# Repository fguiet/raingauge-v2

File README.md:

# Raingauge v2

## The final project

This project is available on Thingiverse : <https://www.thingiverse.com/thing:6480016>

## PCB representation

## 3D representation

## Compute how much water has fell ?

Funnel diameter = 15cm = 150 mm = 0.15m
Volume of each bucket (around) = 3ml = 0.0030l

Funnel area = pi*R² = 3.14 * 0.075² = 0,017669025 m2

X= 1/Aire * V = (1/0,017669025) * 0.0030 = 0.17 L par m2 (ou mm)

1mm = Une litre d'eau tombé sur une mètre carré

Résolution de mon pluvio = 0.17 L/m2 (c'est dans la norme)

## Programming the ATtiny85

Here is the ATtiny 85 pinout

Using Arduino IDE v2, use this tutorial : <https://www.instructables.com/How-to-Program-an-Attiny85-From-an-Arduino-Uno/>

1. Use this following URL to add ATtiny Board to Arduino IE <https://raw.githubusercontent.com/damellis/attiny/ide-1.6.x-boards-manager/package_damellis_attiny_index.json>. File => Preferences => Aditional Board URL
2. Install the ATtiny boards (Board Manager on the menu on the left, then Install)
3. __Burn the ArduinoISP Exemple in the Arduino Board (select Arduino Board)__ => Don't forget that ! and make sure ATTiny pin are well connected to the bread board
4. Select ATtiny 85 board
5. Select Clock Internal 1 Mhz (it is ok for this project)
6. Select Programmer => Arduino as ISP
7. Burn Boatloader
8. Open sketch to upload then click on the menu Sketch => Upload using programmer

A quick overview of the Arduino and ATtiny 85 connexion.

__To program (Arduino <=> ATtiny 85):__

VCC (3.3v ou 5V) <=> VCC (ATtiny pin8)
Arduino GND <=> GND (ATtiny pin4)
Arduino Pin 10 <=> ATtiny Pin1
Arduino Pin 11 <=> ATtiny Pin5
Arduino Pin 12 <=> ATTiny Pin6
Arduino Pin 13 <=> ATTiny Pin7

## Interrupt and power saving stuff with ATtiny 85

See <https://forum.arduino.cc/t/attiny84-sleep-issues/199824/8>
See <http://www.gammon.com.au/power>
See <https://www.marcelpost.com/wiki/index.php/ATtiny84_ADC>

Extract from ATtiny datasheet p49.

²> 9.2 External Interrupts
> Note that recognition of falling or rising edge interrupts on INT0 requires the presence of an
> I/O clock, as described in “Clock Sources” on page 25.

## How to debug using Serial Adapter 

Careful use 3.3v on your serial adapter.

Connect this way:

USB To Serial Adapter <-> ATTiny
GND <-> GND
RX <-> Pin 7 (PB2) 

Then, power the circuit by an external alimentation at 3.3v (no need to power the USB Serial Adapter to VCC pin)

## Power consumption

Using the PPK II (Nordic Power Profiler Kit II), the device consume about 13uA when sleeping and 60mA when sending data.

VOUT of the PPK II should be connected to VIN of the device and GND to GND.

See [Get your Power Profiler Kit II up and running](https://www.youtube.com/watch?v=B42lPvkUSoc)

## Configuring XBee S1 with XCTU v6.5.13

I am using old XBee S1.

At the begining of the project I was using the transparent mode (AT).

But I changed to API Mode as it offers more options (like the RSSI)

### XBee firmware update

Update the XBee firmware with last version using XCTU v6.5.13

Click on Default (To reset XBee to factory default), then Write
Click on Update to upload the last firmware available for this XBee S1 unit

In my case as of 2023/12 :

To make the Xbee talks to each other just config them with the same Channel and PAN (Personnal Area Network ID). Messages will be broadcasted.

### Test XBee communication (deprecated as it shows transparent mode)

You can use XCTU to test that a mesage is correcly sent.

In my case I have got an Raspberry Pi with NodeRed installed and an XBeee connected to the Raspberry Pi.

Just use the XCTU Console and send a test packet, here : "Rainguage projet rocks!" in a JSON format

Here a part of the NodeRed flow I am using.

Careful, you must configure the NodeRed serial flow to split a message as soon as the '}' character is reveiced (end of JSON message)

If everything is going well then you should received the message on the NodeRed debug console

### XBee pinout

### Sleep mode

To config the Xee to use the sleep mode, just change the sleep mode setting

Sleep mode will be control by pin 9, see <https://www.digi.com/resources/documentation/Digidocs/90001456-13/reference/r_wk_sleep_mode.htm>

PIN 9 HIGH : Xbee sleeps
PIN 9 DOWN : Xbee awake

### XBee speed communication

Don't forget to set Xbee serial speed communication to 38400 bauds as the ATtinySerialOut library use this speed.

### New way of communicating : Using the API Mode

I was using Transparent Mode before (AT) but there is another mode called API Mode that offers more options and controls

See [API mode in detail](https://www.digi.com/resources/documentation/Digidocs/90001942-13/concepts/c_api_mode_detailed.htm?TocPath=XBee%20API%20mode%7C_____1)

See [API Mode 2 frame Structure](https://www.digi.com/resources/documentation/Digidocs/90001942-13/concepts/c_api_frame_structure.htm?tocpath=XBee%20API%20mode%7C_____2)C

Supported frames are listed here : <https://www.digi.com/resources/documentation/Digidocs/90001942-13/reference/r_supported_frames_zigbee.htm?tocpath=API%20mode%7C_____3>

I am using the 64-bit Transmit Request - 0x00 frame. I know that I should use the 0x10 frame tpye but I am using old XBee S1 and they only support 802.15.4 protocol stack.

See [64-bit Transmit Request - 0x00](https://www.digi.com/resources/documentation/Digidocs/90001477/reference/r_frame_0x00.htm?tocpath=API%20frames%7C_____3)

In API Mode 2, some characters need to be escaped:

See : <https://stackoverflow.com/questions/55861574/difference-between-api-1-and-api-2-mode-of-xbee>

* 0x7E (Start of frame) => 0x7D 0x5E (escaped)
* 0x7D (start of escape sequence) => 0x7D 0x5D (escaped)
* 0x13 (XOFF) => 0x7D 0x33 (escaped)
* 0x11 (XON) =>	0x7D 0x31 (escaped)

In API 2 mode, the length field does not include any escape character in the frame and the checksum is calculated with non-escaped data.

All bytes except for the start delimiter must be escaped if needed.

* End Device XBee configuration

Here is what I changed in the XBee configuration with XCTU

CH - Channel = C
ID - PAN ID = 666
SM - Sleep mode = Pin Hibernate [1]
BD - Interface Data Rate = 38400 [5]
AP - API Enable = API Enabled w/PPP [2]

* Coordinator XBee configuration

CH - Channel = C
ID - PAN ID = 666
CE - Coordinator Enable = Coordinator [1]
BD - Interface Data Rate = 38400 [5]
AP - API Enable = API Enabled w/PPP [2]
RR - XBee Retries = 3 (because the RSSI was not good I tried this setting)

## Librairies used in this project

* ATTinySerialOut

To communicate with the XBee (send data), this project used the following library : `ATtinySerialOut`, version 2.2.0 (2023/12)

GitHub : <https://github.com/ArminJo/ATtinySerialOut/>

* LowPower

This project is using this library <https://github.com/ortegafernando/Low-Power> to allow the ATTiny 85 power management

__Note__

To use an external library for a Arduino IDE Project, just copy the library source in the librairies folder of Arduino IDE

## Freecad

__Some notes__

* On ne peut pas utiliser le mirroring sur la pièce que l'on veut "mirrorer" n'a pas de lien avec un objet du body en cours (pas de corps multiples dans un body)

* Utilisation de ShapeBinder pour pouvoir avoir des points de repères d'un autre body (voir vidéo : <https://www.youtube.com/watch?v=KYD9Ojugi8Q>)

### Support tipping bucket

Les trous pour placer les inserts font 4.2mm sur Freecad. les inserts à utiliser sont des M3*4 (4 mm de haut pour type vis M3)

## Pull up / pull down

Quick reminder about pullup/pulldown : <https://arduino.developpez.com/cahiers-pratiques/resistance-pullup-pulldown/>

## Kicad

Ce tuto : <https://www.youtube.com/watch?v=RpVIrzEUsIM> ou <https://www.youtube.com/watch?v=dAck3bxzehA> ou <https://www.youtube.com/watch?v=nYybg5KdaT8>

__Note__ :

Suppression du snap sur le PCB Editor afin de placer les composants à un endroits précis : utiliser la touche CTRL

__Grandes étapes__

1. Editeur de schéma électronique, remplir le cartouche pour définir les informations du PCB

Fichier, Ajustage page

2. Place all your components

Shortcut

M : Move
R : Rotate
Tab  : Pour bouger le composant avec les fils accrochés

Pour vérifier que le circuit est ok on peut cliquer sur le bouton : 

__Note__

* Essayer de mettre par convention VCC en haut et GND en bas au niveau du positionnement
* Il existe des labels global et local (A voir sur le net la différence)
* Possibilité de créer des feuilles hiérarchiques (si jamais on a un schéma très grand alors on peut le splitter, après y'a les notions de labels hiérarchiques, global, etc etc...)
* Il faut bien penser à définir les pins qui alimentent le schéma électrique (= PWR_FLAG)

3. Annotation de la schématique (pour numéroter les composants)

Normalement avec Kicad 7, les éléments sont numérotés automatiquement.
Sinon, cliquer sur le bouton: 

4. Assigner les empreintes des composants de la schématique

5. Génération de la net liste

Inutile dans Kicad 7 ?

6. Editeur de circuit imprimé et lecture de la net liste

Inutile dans Kicad 7 ?

7. Placement des composants sur l'éditeur de PBB

On passe sur cet écran en cliquant sur :

Récupération des contraintes JLCPCB : <https://github.com/sethhillbrand/kicad_templates/tree/master/JLCPCB_1-2Layer> prendre le fichier JLCPCB.pro

Fichier, Ajustage page pour personnaliser le cartouche comme pour l'éditeur de schéma électronique

Pour gérer la largeur des pistes en fonction du type de piste (VCC) : Fichiers, Options CI, Classe d'Equipots, j'utilise 0.4mm pour les pistes classiques et 0.8mm en VCC

Penser à modifier la valeur par défault de la largeur des pistes à 0.4mm

Short Cut

v: change layer (front / bottom)

__Notes__

Layers intéressantes 

F. Silks pour écrire sur le front Silk Screen
B. Silks pour écrire sur le bottom Silk Screen
Dwgs.User pour faire des dessins
F. Courtyard : place que prend le composant front
B. Courtyard : place que prend le composant bottom (on peut afficher ou pas)

Quand il y a beaucoup d'éléments sur le PCB, on peut utiliser le filtre de sélection afin de limiter la sélection à l'objet que l'on désire (exemple j'avais besoin de bouger les références des composants sur la layer silkscreen)

8. Couche Edge cut (contour de carte)

On trace autour des composants pour couper le PCB à la taille désirée

9. Routage

Pour la largeur, bien penser à sélectionner utiliser largeur de netclasse.
Attention, dans netclasse il faut avoir penser à modifier la valeur par défaut pour la largeur des pistes à 0.4mm et mettre 0.8mm pour les pistes de puissance (PWR)

Voici ce qu'il faut respecter lors que l'on trace des routages pour éviter les pbs d'électromagnétisme.

Quand on a des tracks qui se croisent sur la couche du dessus et dessous il faut qu'elles soient perpendiculaires:

Couche F. Cu (Front en rouge couche du dessus)
Couche B. Cu (Front en vert couche du dessous)

Ne pas relier les GND, ca sera automatique avec le plan de masse

__Notes__

Short cut

D : Pour modifer les tracks sans tous casser
I : Au dessus d'une track permet de sélectionner toute la track

10. Ajouter la zone ground (sur layer front / bottom)

Utiliser l'outil : 

10. Serigrafie avec couche Drawing User pour mettre les indications + - et autres ou layer F. Silks et B. Silks

11. Générer les fichiers Gerber, Fichier Tracer (ne pas oublier de générer le fichier de percage)

Mettre un texte JLCJLCJLCJLC sous un composant (layersilk screen)

D'abord générer le fichier de percage (generate drill file) et ensuite plot avec les options par défaut.

12. Faire un Zip et envoyer sur JLCPCB par exemple

## References

* snapeda pour récupérer des composants kicad : <https://www.snapeda.com/>

* Madman's Github : <https://github.com/PricelessToolkit/MailBoxGuard>

* ATTiny and LoRa : <https://github.com/novag/LoRa-ATtiny-Node>

* MrDIY : <https://gitlab.com/MrDIYca/ultra-low-power-trigger-sensors-version-3>

* [MakerMeik : ESP8266 as Window Sensor with years of battery life](https://www.youtube.com/watch?v=vxbuO1zWo3w)

* [ESP32-C3 based Smart Door/Window sensor | DEEP SLEEP 30nA? | Long battery life 5/10 years](https://www.youtube.com/watch?v=he_Z-mDLnlM)

* [Raingauge version 1](https://www.youtube.com/watch?v=DnNW4rJkFhY&t=649s)

* [Raingauge version 2](https://www.youtube.com/watch?v=P2-hs2m6eCE)

* [Communication XBee](https://www.redohm.fr/2015/03/communication-xbee/)

* [Configuration XBee](https://www.electro-info.ovh/configuration-d-un-module-XBEE-avec-XCTU)

* [Un programme qui ressemble a ce que je fais](https://github.com/cano64/ATTiny85-ATTiny84-BMP085-Arduino-Library-FastAltitude/issues/1)

* [How works a switch without neutral](https://www.youtube.com/watch?v=VNYcD7MEp4A)

* [Inspiring sketch : OpenWindowAlarm](https://github.com/ArminJo/ATtinySerialOut/blob/master/examples/OpenWindowAlarm/OpenWindowAlarm.ino)

* [OpenWindowAlarm documentation](https://github.com/ArminJo/Arduino-OpenWindowAlarm)

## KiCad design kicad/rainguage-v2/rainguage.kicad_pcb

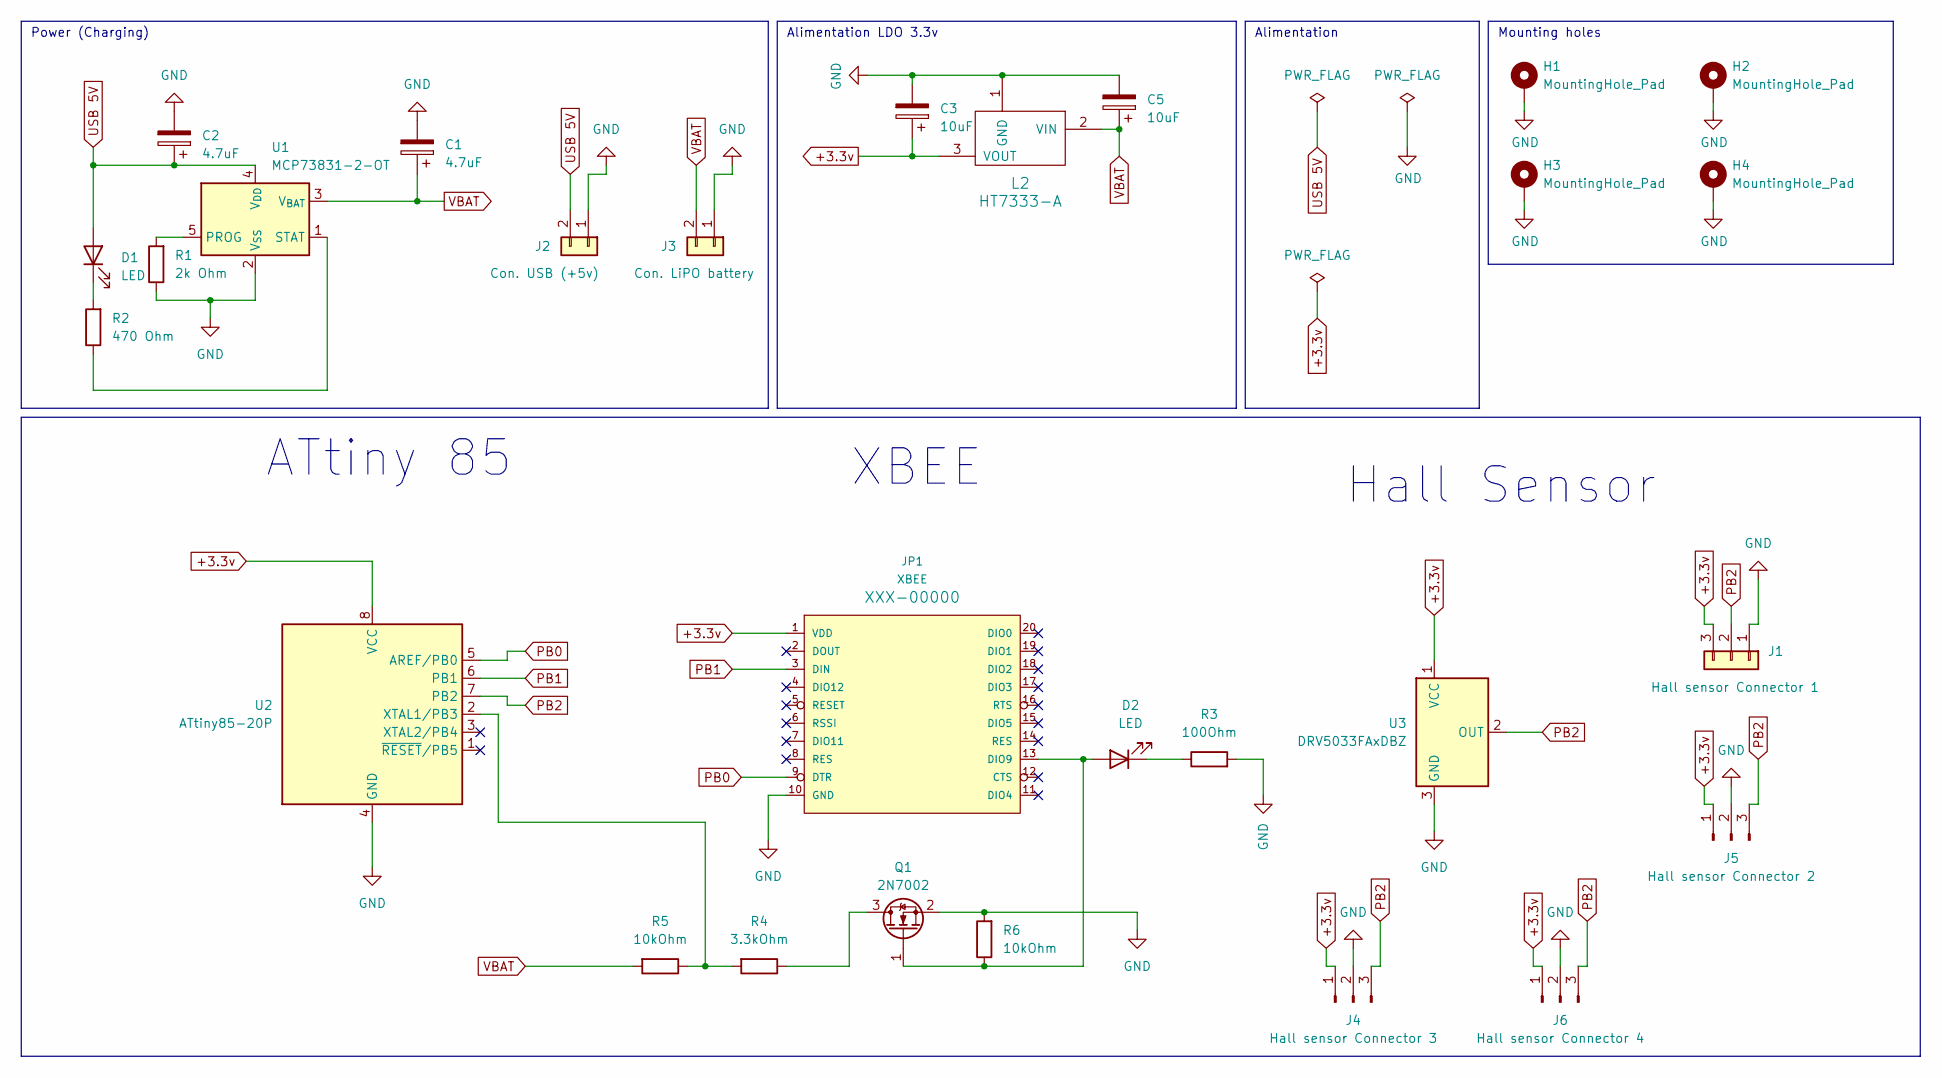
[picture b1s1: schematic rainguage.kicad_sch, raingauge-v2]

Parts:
C1, C2: 4.7uF; C_0805_2012Metric
C3, C5: 10uF; C_0805_2012Metric
D1, D2: LED; LED_0805_2012Metric
H1, H2, H3, H4: MountingHole_Pad; MountingHole_2.2mm_M2_Pad
J1: Hall sensor Connector 1; JST_EH_B3B-EH-A_1x03_P2.50mm_Vertical
J2: Con. USB (+5v); JST_EH_B2B-EH-A_1x02_P2.50mm_Vertical
J3: Con. LiPO battery; JST_EH_B2B-EH-A_1x02_P2.50mm_Vertical
J4: Hall sensor Connector 3; PinSocket_1x03_P2.54mm_Vertical
J5: Hall sensor Connector 2; PinSocket_1x03_P2.54mm_Vertical
J6: Hall sensor Connector 4; PinSocket_1x03_P2.54mm_Vertical
JP1: XBEE
L2: HT7333-A; SOT-89-3
Q1: 2N7002; SOT-23
R1: 2k Ohm; R_0805_2012Metric
R2: 470 Ohm; R_0805_2012Metric
R3: 100Ohm; R_0805_2012Metric
R4: 3.3kOhm; R_0805_2012Metric
R5, R6: 10kOhm; R_0805_2012Metric
U1: MCP73831-2-OT; SOT-23-5
U2: ATtiny85-20P; DIP-8_W7.62mm
U3: DRV5033FAxDBZ; SOT-23

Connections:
+3.3v: C3.1, J1.3, J4.1, J5.1, J6.1, JP1.1 (VDD), L2.3 (VOUT), U2.8 (VCC), U3.1 (VCC)
GND: C1.2, C2.2, C3.2, C5.2, H1.1, H2.1, H3.1, H4.1, J1.1, J2.1, J3.1, J4.2, J5.2, J6.2, JP1.10 (GND), L2.1 (GND), Q1.2 (S), R1.1, R3.2, R6.2, U1.2 (V_{SS}), U2.4 (GND), U3.3 (GND)
unnamed: D1.1 (K), R2.2
unnamed: D2.2 (A), JP1.13 (DIO9), Q1.1 (G), R6.1
unnamed: D2.1 (K), R3.1
unnamed: Q1.3 (D), R4.1
unnamed: R1.2, U1.5 (PROG)
unnamed: R2.1, U1.1 (STAT)
unnamed: R4.2, R5.1, U2.2 (XTAL1/PB3)
PB0: JP1.9 (DTR), U2.5 (AREF/PB0)
PB1: JP1.3 (DIN), U2.6 (PB1)
PB2: J1.2, J4.3, J5.3, J6.3, U2.7 (PB2), U3.2 (OUT)
USB 5V: C2.1, D1.2 (A), J2.2, U1.4 (V_{DD})
VBAT: C1.1, C5.1, J3.2, L2.2 (VIN), R5.2, U1.3 (V_{BAT})

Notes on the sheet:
XBEE
Power (Charging)
Hall Sensor
Mounting holes
Alimentation
Alimentation LDO 3.3v
ATtiny 85

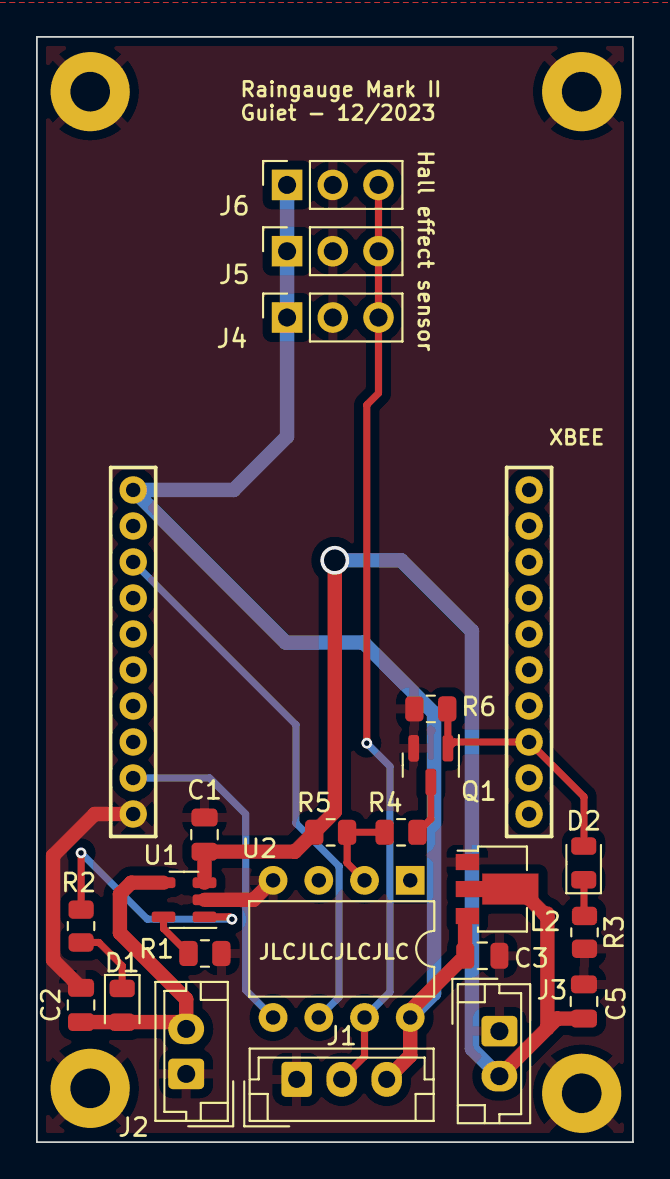
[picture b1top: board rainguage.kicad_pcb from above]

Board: 2 copper layers, 33.1 x 61.4 mm, 27 parts (0 on the bottom side), 14 nets.

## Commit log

2023-12-23 First commit of this fabulous project ;-)
2023-12-26 Update doc
2023-12-28 Petit commit des familles
2023-12-28 commit des familles
2023-12-31 add 3d representation
2024-01-20 Add arduino ide sketch
2024-01-24 push last updates
2024-02-11 add thingiverse link
2024-02-18 use variable to store coordinator address
2024-03-09 Update freecad design
